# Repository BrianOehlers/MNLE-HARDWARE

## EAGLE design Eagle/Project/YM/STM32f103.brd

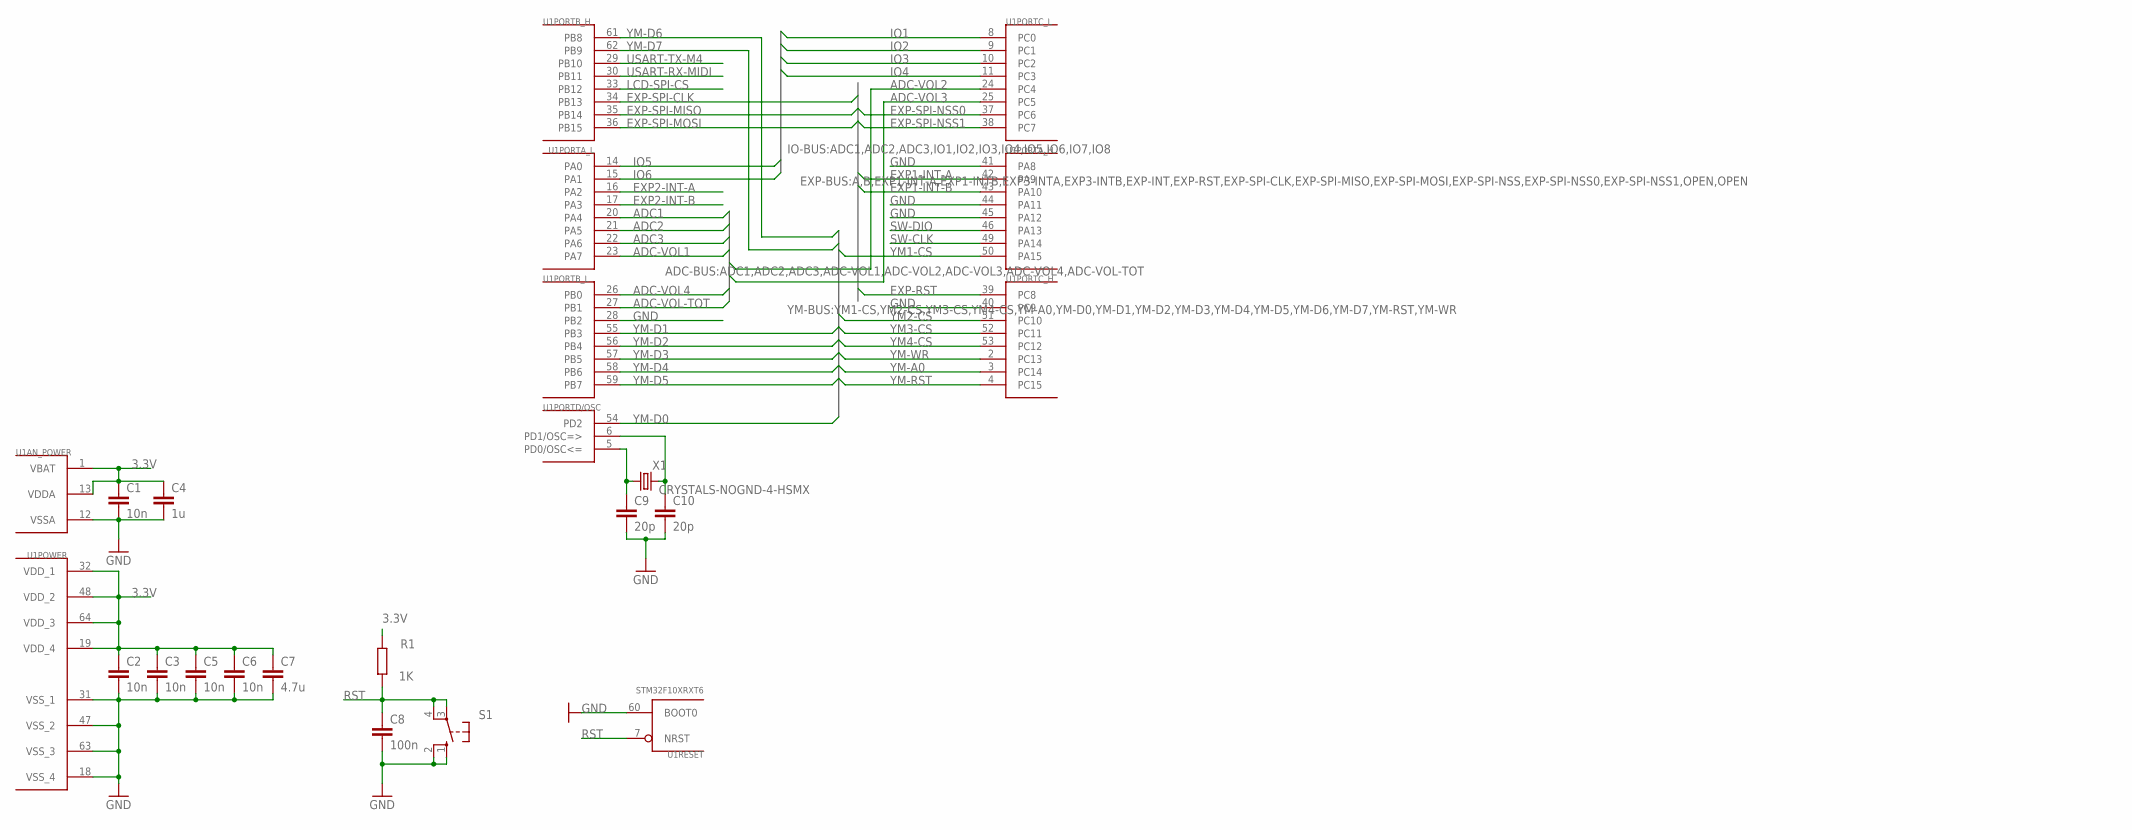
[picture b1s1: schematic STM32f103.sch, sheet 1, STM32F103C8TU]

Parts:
C1, C2, C3, C5, C6: 10n; C0603
C4: 1u; C0603
C7: 4.7u; C0603
C8: 100n; 0603-SMD
C9, C10: 20p; C0603
R1: 1K; 0805-SMD
S1: 10-XX; B3F-10XX
U1: STM32F10XRXT6; TQFP64
X1: CRYSTALS-NOGND-4-HSMX; HC49-4-HSMX

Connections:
3.3V: C1.1, C2.1, C3.1, C4.1, C5.1, C6.1, C7.1, R1.2, U1.1 (VBAT), U1.13 (VDDA), U1.19 (VDD_4), U1.32 (VDD_1), U1.48 (VDD_2), U1.64 (VDD_3); also elsewhere on the board
ADC1: U1.20 (PA4); also elsewhere on the board
ADC2: U1.21 (PA5); also elsewhere on the board
ADC3: U1.22 (PA6); also elsewhere on the board
ADC-VOL1: U1.23 (PA7); also elsewhere on the board
ADC-VOL2: U1.24 (PC4); also elsewhere on the board
ADC-VOL3: U1.25 (PC5); also elsewhere on the board
ADC-VOL4: U1.26 (PB0); also elsewhere on the board
ADC-VOL-TOT: U1.27 (PB1); also elsewhere on the board
EXP1-INT-A: U1.42 (PA9); also elsewhere on the board
EXP1-INT-B: U1.43 (PA10); also elsewhere on the board
EXP2-INT-A: U1.16 (PA2); also elsewhere on the board
EXP2-INT-B: U1.17 (PA3); also elsewhere on the board
EXP-RST: U1.39 (PC8); also elsewhere on the board
EXP-SPI-CLK: U1.34 (PB13); also elsewhere on the board
EXP-SPI-MISO: U1.35 (PB14); also elsewhere on the board
EXP-SPI-MOSI: U1.36 (PB15); also elsewhere on the board
EXP-SPI-NSS0: U1.37 (PC6); also elsewhere on the board
EXP-SPI-NSS1: U1.38 (PC7); also elsewhere on the board
GND: C1.2, C2.2, C3.2, C4.2, C5.2, C6.2, C7.2, C8.2, C9.2, C10.2, S1.1 (S), S1.2 (S1), U1.12 (VSSA), U1.18 (VSS_4), U1.28 (PB2), U1.31 (VSS_1), U1.40 (PC9), U1.41 (PA8), U1.44 (PA11), U1.45 (PA12), U1.47 (VSS_2), U1.60 (BOOT0), U1.63 (VSS_3); also elsewhere on the board
IO1: U1.8 (PC0); also elsewhere on the board
IO2: U1.9 (PC1); also elsewhere on the board
IO3: U1.10 (PC2); also elsewhere on the board
IO4: U1.11 (PC3); also elsewhere on the board
IO5: U1.14 (PA0); also elsewhere on the board
IO6: U1.15 (PA1); also elsewhere on the board
LCD-SPI-CS: U1.33 (PB12); also elsewhere on the board
unnamed: C9.1, U1.5 (PD0/OSC<=), X1.1
unnamed: C10.1, U1.6 (PD1/OSC=>), X1.2
RST: C8.1, R1.1, S1.3, S1.4 (P1), U1.7 (NRST)
SW-CLK: U1.49 (PA14); also elsewhere on the board
SW-DIO: U1.46 (PA13); also elsewhere on the board
USART-RX-MIDI: U1.30 (PB11); also elsewhere on the board
USART-TX-M4: U1.29 (PB10); also elsewhere on the board
YM1-CS: U1.50 (PA15); also elsewhere on the board
YM2-CS: U1.51 (PC10); also elsewhere on the board
YM3-CS: U1.52 (PC11); also elsewhere on the board
YM4-CS: U1.53 (PC12); also elsewhere on the board
YM-A0: U1.3 (PC14); also elsewhere on the board
YM-D0: U1.54 (PD2); also elsewhere on the board
YM-D1: U1.55 (PB3); also elsewhere on the board
YM-D2: U1.56 (PB4); also elsewhere on the board
YM-D3: U1.57 (PB5); also elsewhere on the board
YM-D4: U1.58 (PB6); also elsewhere on the board
YM-D5: U1.59 (PB7); also elsewhere on the board
YM-D6: U1.61 (PB8); also elsewhere on the board
YM-D7: U1.62 (PB9); also elsewhere on the board
YM-RST: U1.4 (PC15); also elsewhere on the board
YM-WR: U1.2 (PC13); also elsewhere on the board

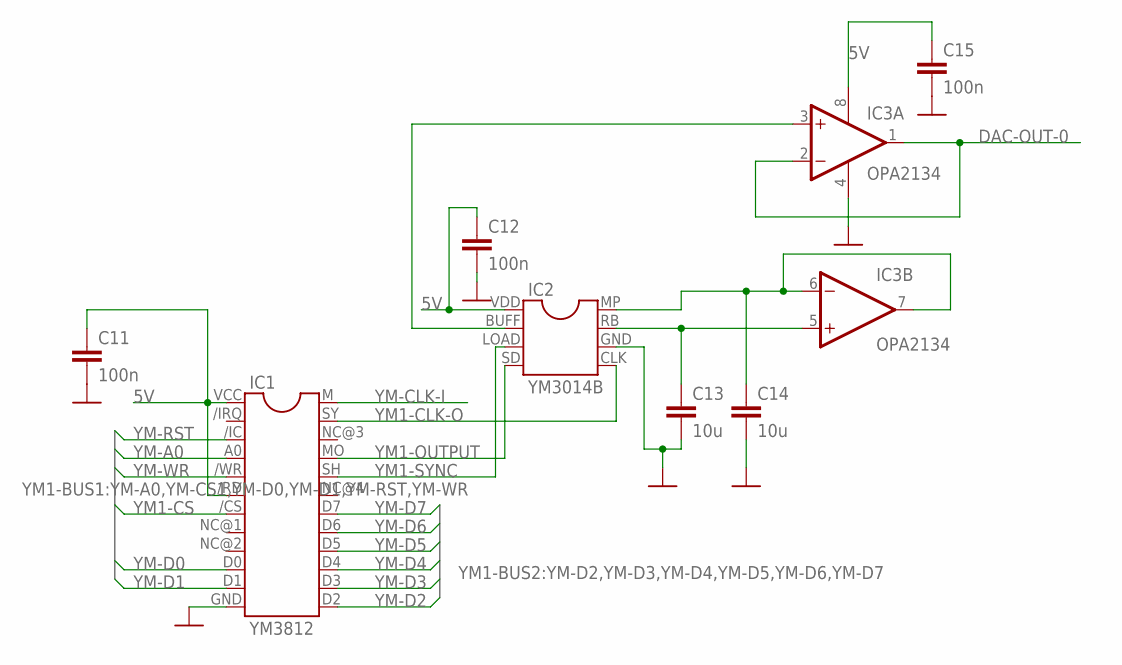
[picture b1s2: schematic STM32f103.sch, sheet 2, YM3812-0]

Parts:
C11, C12, C15: 100n; 0603-SMD
C13, C14: 10u; 0603-SMD
IC1: YM3812
IC2: YM3014B
IC3: OPA2134; DIL08

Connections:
5V: C11.1, C12.1, C15.1, IC1./RD, IC1.VCC, IC2.VDD, IC3.8 (V+); also elsewhere on the board
DAC-OUT-0: IC3.1 (OUT), IC3.2 (-IN); also elsewhere on the board
GND: C11.2, C12.2, C13.2, C14.2, C15.2, IC1.GND, IC2.GND, IC3.4 (V-); also elsewhere on the board
unnamed: IC2.BUFF, IC3.3 (+IN)
unnamed: C14.1, IC2.MP, IC3.6 (-IN), IC3.7 (OUT)
unnamed: C13.1, IC2.RB, IC3.5 (+IN)
YM1-CLK-O: IC1.SY, IC2.CLK
YM1-CS: IC1./CS; also elsewhere on the board
YM1-OUTPUT: IC1.MO, IC2.SD; also elsewhere on the board
YM1-SYNC: IC1.SH, IC2.LOAD; also elsewhere on the board
YM-A0: IC1.A0; also elsewhere on the board
YM-CLK-I: IC1.M; also elsewhere on the board
YM-D0: IC1.D0; also elsewhere on the board
YM-D1: IC1.D1; also elsewhere on the board
YM-D2: IC1.D2; also elsewhere on the board
YM-D3: IC1.D3; also elsewhere on the board
YM-D4: IC1.D4; also elsewhere on the board
YM-D5: IC1.D5; also elsewhere on the board
YM-D6: IC1.D6; also elsewhere on the board
YM-D7: IC1.D7; also elsewhere on the board
YM-RST: IC1./IC; also elsewhere on the board
YM-WR: IC1./WR; also elsewhere on the board

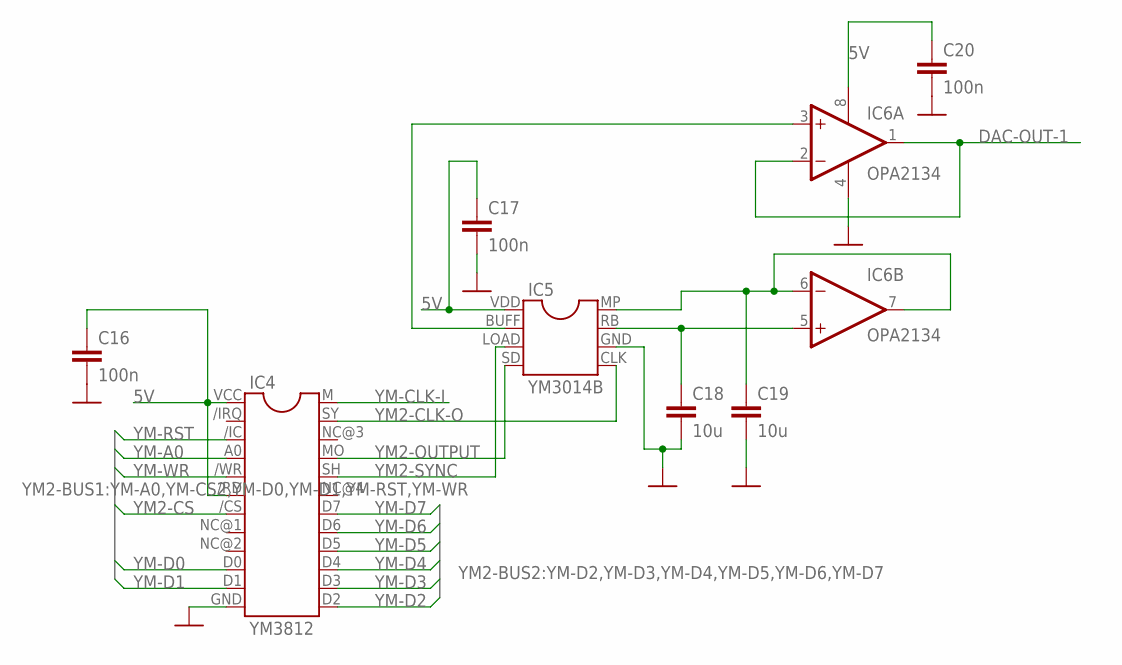
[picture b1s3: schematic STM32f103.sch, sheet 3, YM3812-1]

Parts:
C16, C17, C20: 100n; 0603-SMD
C18, C19: 10u; 0603-SMD
IC4: YM3812
IC5: YM3014B
IC6: OPA2134; DIL08

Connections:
5V: C16.1, C17.1, C20.1, IC4./RD, IC4.VCC, IC5.VDD, IC6.8 (V+); also elsewhere on the board
DAC-OUT-1: IC6.1 (OUT), IC6.2 (-IN); also elsewhere on the board
GND: C16.2, C17.2, C18.2, C19.2, C20.2, IC4.GND, IC5.GND, IC6.4 (V-); also elsewhere on the board
unnamed: C18.1, IC5.RB, IC6.5 (+IN)
unnamed: IC5.BUFF, IC6.3 (+IN)
unnamed: C19.1, IC5.MP, IC6.6 (-IN), IC6.7 (OUT)
YM2-CLK-O: IC4.SY, IC5.CLK
YM2-CS: IC4./CS; also elsewhere on the board
YM2-OUTPUT: IC4.MO, IC5.SD; also elsewhere on the board
YM2-SYNC: IC4.SH, IC5.LOAD; also elsewhere on the board
YM-A0: IC4.A0; also elsewhere on the board
YM-CLK-I: IC4.M; also elsewhere on the board
YM-D0: IC4.D0; also elsewhere on the board
YM-D1: IC4.D1; also elsewhere on the board
YM-D2: IC4.D2; also elsewhere on the board
YM-D3: IC4.D3; also elsewhere on the board
YM-D4: IC4.D4; also elsewhere on the board
YM-D5: IC4.D5; also elsewhere on the board
YM-D6: IC4.D6; also elsewhere on the board
YM-D7: IC4.D7; also elsewhere on the board
YM-RST: IC4./IC; also elsewhere on the board
YM-WR: IC4./WR; also elsewhere on the board

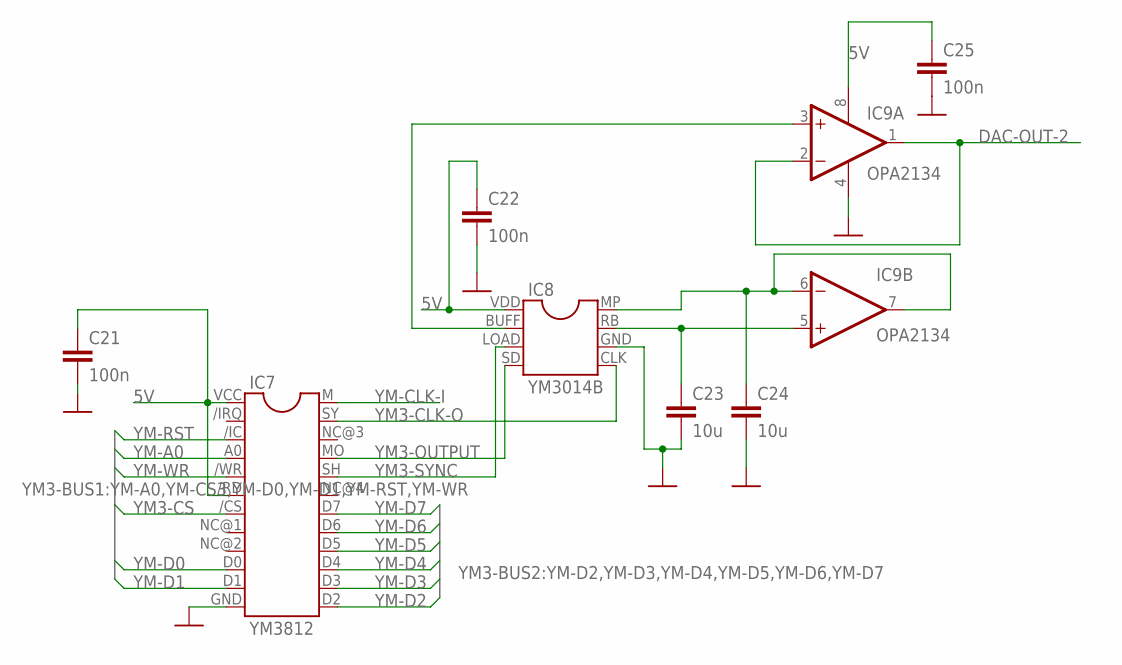
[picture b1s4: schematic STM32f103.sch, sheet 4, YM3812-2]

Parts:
C21, C22, C25: 100n; 0603-SMD
C23, C24: 10u; 0603-SMD
IC7: YM3812
IC8: YM3014B
IC9: OPA2134; DIL08

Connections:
5V: C21.1, C22.1, C25.1, IC7./RD, IC7.VCC, IC8.VDD, IC9.8 (V+); also elsewhere on the board
DAC-OUT-2: IC9.1 (OUT), IC9.2 (-IN); also elsewhere on the board
GND: C21.2, C22.2, C23.2, C24.2, C25.2, IC7.GND, IC8.GND, IC9.4 (V-); also elsewhere on the board
unnamed: C23.1, IC8.RB, IC9.5 (+IN)
unnamed: IC8.BUFF, IC9.3 (+IN)
unnamed: C24.1, IC8.MP, IC9.6 (-IN), IC9.7 (OUT)
YM3-CLK-O: IC7.SY, IC8.CLK
YM3-CS: IC7./CS; also elsewhere on the board
YM3-OUTPUT: IC7.MO, IC8.SD; also elsewhere on the board
YM3-SYNC: IC7.SH, IC8.LOAD; also elsewhere on the board
YM-A0: IC7.A0; also elsewhere on the board
YM-CLK-I: IC7.M; also elsewhere on the board
YM-D0: IC7.D0; also elsewhere on the board
YM-D1: IC7.D1; also elsewhere on the board
YM-D2: IC7.D2; also elsewhere on the board
YM-D3: IC7.D3; also elsewhere on the board
YM-D4: IC7.D4; also elsewhere on the board
YM-D5: IC7.D5; also elsewhere on the board
YM-D6: IC7.D6; also elsewhere on the board
YM-D7: IC7.D7; also elsewhere on the board
YM-RST: IC7./IC; also elsewhere on the board
YM-WR: IC7./WR; also elsewhere on the board

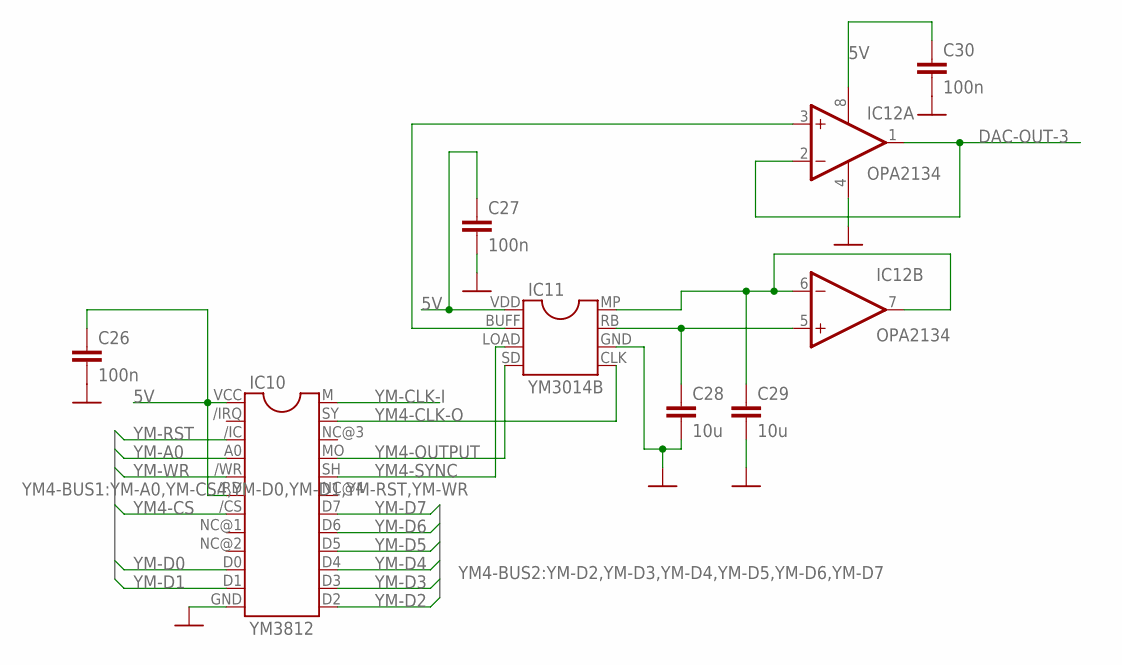
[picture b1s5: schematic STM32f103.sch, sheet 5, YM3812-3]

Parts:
C26, C27, C30: 100n; 0603-SMD
C28, C29: 10u; 0603-SMD
IC10: YM3812
IC11: YM3014B
IC12: OPA2134; DIL08

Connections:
5V: C26.1, C27.1, C30.1, IC10./RD, IC10.VCC, IC11.VDD, IC12.8 (V+); also elsewhere on the board
DAC-OUT-3: IC12.1 (OUT), IC12.2 (-IN); also elsewhere on the board
GND: C26.2, C27.2, C28.2, C29.2, C30.2, IC10.GND, IC11.GND, IC12.4 (V-); also elsewhere on the board
unnamed: C28.1, IC11.RB, IC12.5 (+IN)
unnamed: IC11.BUFF, IC12.3 (+IN)
unnamed: C29.1, IC11.MP, IC12.6 (-IN), IC12.7 (OUT)
YM4-CLK-O: IC10.SY, IC11.CLK
YM4-CS: IC10./CS; also elsewhere on the board
YM4-OUTPUT: IC10.MO, IC11.SD; also elsewhere on the board
YM4-SYNC: IC10.SH, IC11.LOAD; also elsewhere on the board
YM-A0: IC10.A0; also elsewhere on the board
YM-CLK-I: IC10.M; also elsewhere on the board
YM-D0: IC10.D0; also elsewhere on the board
YM-D1: IC10.D1; also elsewhere on the board
YM-D2: IC10.D2; also elsewhere on the board
YM-D3: IC10.D3; also elsewhere on the board
YM-D4: IC10.D4; also elsewhere on the board
YM-D5: IC10.D5; also elsewhere on the board
YM-D6: IC10.D6; also elsewhere on the board
YM-D7: IC10.D7; also elsewhere on the board
YM-RST: IC10./IC; also elsewhere on the board
YM-WR: IC10./WR; also elsewhere on the board

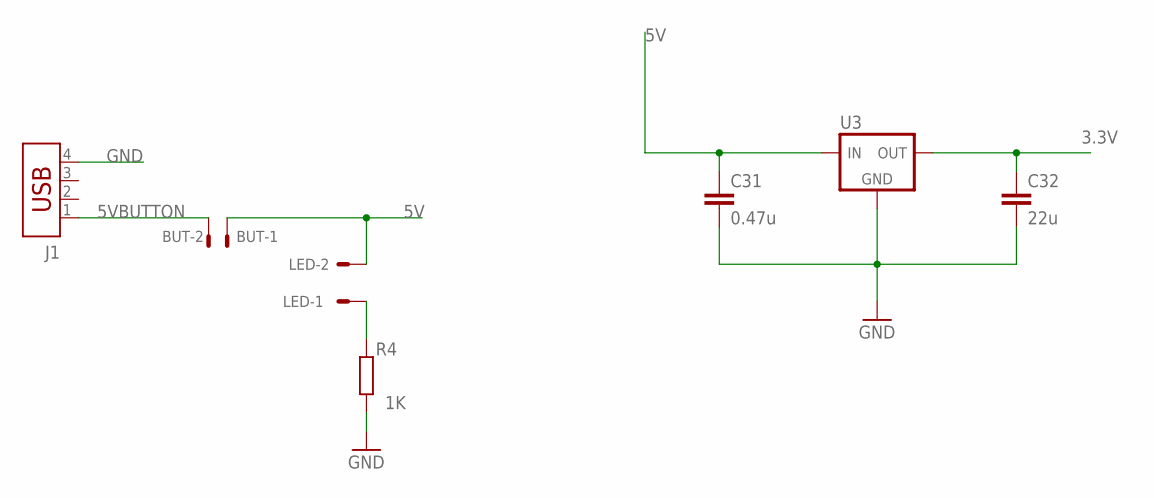
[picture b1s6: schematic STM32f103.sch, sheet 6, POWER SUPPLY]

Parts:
BUT: 22-27-2021-02; 6410-02
C31: 0.47u; 0603-SMD
C32: 22u; 0603-SMD
J1: CON-USB-B; USB-B
LED: 22-27-2021-02; 6410-02
R4: 1K; 0805-SMD
U3: LM2931AT-H; TO220BH

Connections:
3.3V: C32.1, U3.3 (VOUT); also elsewhere on the board
5V: BUT.1, C31.1, LED.2, U3.1 (VIN); also elsewhere on the board
5VBUTTON: BUT.2, J1.1
GND: C31.2, C32.2, J1.4, R4.2, U3.2 (GND); also elsewhere on the board
unnamed: LED.1, R4.1

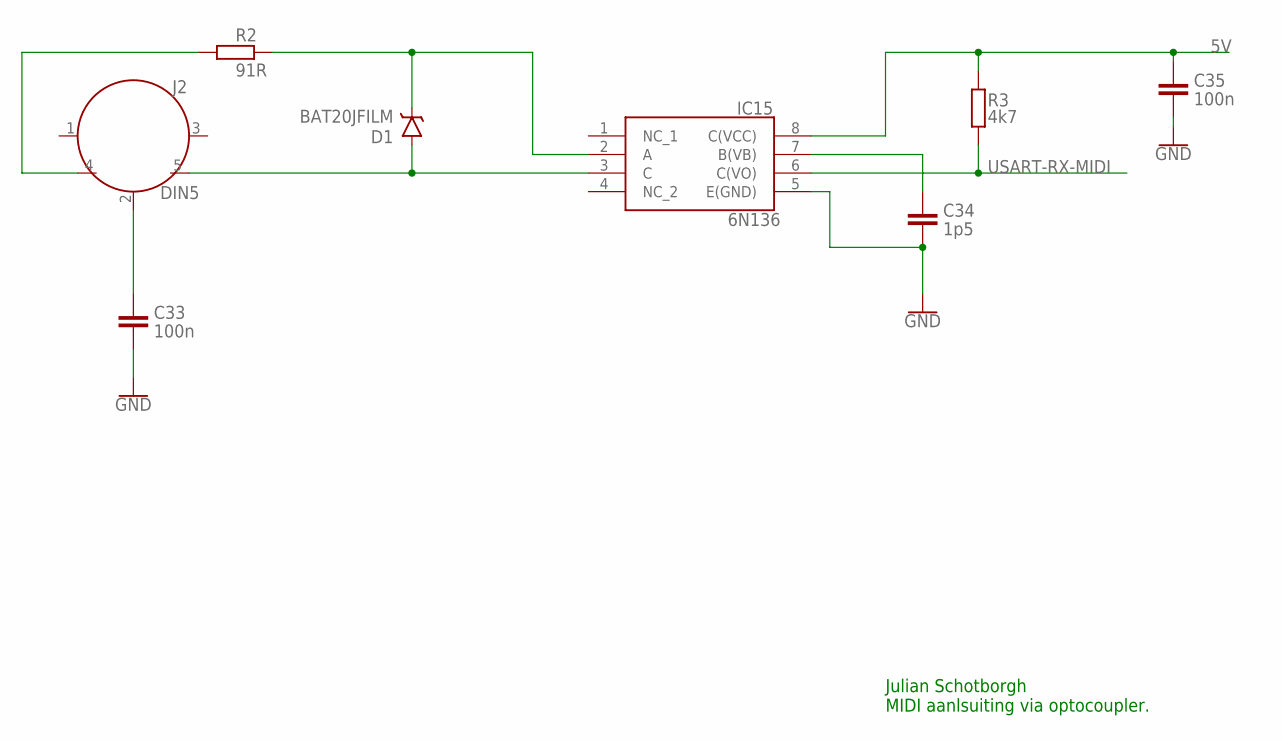
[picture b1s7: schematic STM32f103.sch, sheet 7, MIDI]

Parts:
C33, C35: 100n; C0603
C34: 1p5; C0603
D1: BAT20JFILM; SOD-323
IC15: 6N136; DIP762W60P254L1060H465Q8N
J2: DIN5; DIN5-RA-PTH
R2: 91R; 0805-SMD
R3: 4k7; 0805-SMD

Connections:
5V: C35.2, IC15.8 (C(VCC)), R3.1; also elsewhere on the board
GND: C33.2, C34.1, C35.1, IC15.5 (E(GND)); also elsewhere on the board
unnamed: D1.A, IC15.3 (C), J2.5
unnamed: D1.C, IC15.2 (A), R2.2
unnamed: C33.1, J2.2
unnamed: J2.4, R2.1
unnamed: C34.2, IC15.7 (B(VB))
USART-RX-MIDI: IC15.6 (C(VO)), R3.2; also elsewhere on the board

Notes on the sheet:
Julian Schotborgh MIDI aanlsuiting via optocoupler.

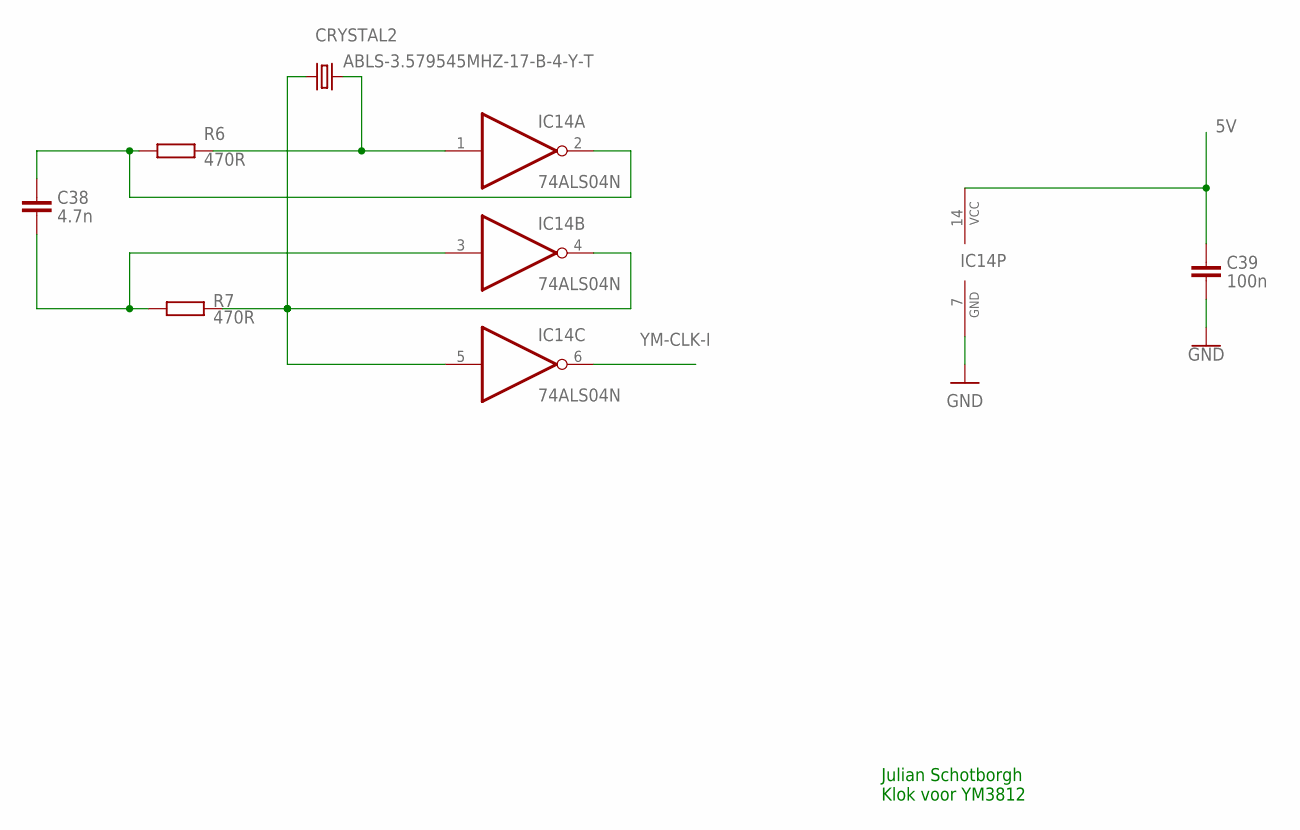
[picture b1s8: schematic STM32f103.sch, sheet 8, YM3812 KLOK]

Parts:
C38: 4.7n; C0603
C39: 100n; C0603
CRYSTAL2: ABLS-3.579545MHZ-17-B-4-Y-T; ABLS-3.579545MHZ-17-B-4-Y-T-11.5X4.7X4.2
IC14: 74ALS04N; DIL14
R6, R7: 470R; 0805-SMD

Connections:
5V: C39.2, IC14.14 (VCC); also elsewhere on the board
GND: C39.1, IC14.7 (GND); also elsewhere on the board
unnamed: CRYSTAL2.P$1 (1), IC14.4 (O), IC14.5 (I), R7.2
unnamed: C38.2, IC14.2 (O), R6.1
unnamed: C38.1, IC14.3 (I), R7.1
unnamed: CRYSTAL2.P$2 (2), IC14.1 (I), R6.2
YM-CLK-I: IC14.6 (O); also elsewhere on the board

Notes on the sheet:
Julian Schotborgh Klok voor YM3812

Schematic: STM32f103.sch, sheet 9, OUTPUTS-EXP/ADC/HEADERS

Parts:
SL1, SL2, SL3, SL4, SL5, SL6, SL7, SL8: MA03; 03P
SL9: M06; 06P
SV2: MA04-1
SV3: 2514-6002UB; 3M_2514-6002UB
SV4: FE13-1; FE13
SV6: FE06-1; FE06
SV7: FE12-1; FE12

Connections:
3.3V: SL1.1, SL2.1, SL3.1, SL4.1, SL5.1, SL6.1, SL7.1, SL8.1, SV2.1, SV3.4, SV4.2, SV4.12; also elsewhere on the board
5V: SL9.5, SV3.3, SV4.3, SV4.13, SV7.11; also elsewhere on the board
ADC1: SL6.2; also elsewhere on the board
ADC2: SL7.2; also elsewhere on the board
ADC3: SL8.2; also elsewhere on the board
ADC-VOL1: SL2.2; also elsewhere on the board
ADC-VOL2: SL3.2; also elsewhere on the board
ADC-VOL3: SL4.2; also elsewhere on the board
ADC-VOL4: SL5.2; also elsewhere on the board
ADC-VOL-TOT: SL1.2; also elsewhere on the board
DAC-OUT-0: SV6.1; also elsewhere on the board
DAC-OUT-1: SV6.2; also elsewhere on the board
DAC-OUT-2: SV6.3; also elsewhere on the board
DAC-OUT-3: SV6.4; also elsewhere on the board
EXP1-INT-A: SV3.8; also elsewhere on the board
EXP1-INT-B: SV3.7; also elsewhere on the board
EXP2-INT-A: SV3.5; also elsewhere on the board
EXP2-INT-B: SV3.6; also elsewhere on the board
EXP-RST: SV3.9; also elsewhere on the board
EXP-SPI-CLK: SL9.2, SV3.14; also elsewhere on the board
EXP-SPI-MISO: SL9.3, SV3.13; also elsewhere on the board
EXP-SPI-MOSI: SL9.4, SV3.12; also elsewhere on the board
EXP-SPI-NSS0: SV3.11; also elsewhere on the board
EXP-SPI-NSS1: SV3.10; also elsewhere on the board
GND: SL1.3, SL2.3, SL3.3, SL4.3, SL5.3, SL6.3, SL7.3, SL8.3, SL9.6, SV2.4, SV3.2, SV4.1, SV4.11, SV6.6, SV7.12; also elsewhere on the board
IO1: SV4.10; also elsewhere on the board
IO2: SV4.9; also elsewhere on the board
IO3: SV4.8; also elsewhere on the board
IO4: SV4.7; also elsewhere on the board
IO5: SV4.6; also elsewhere on the board
IO6: SV4.5; also elsewhere on the board
LCD-SPI-CS: SL9.1; also elsewhere on the board
OPEN: SV3.1
SW-CLK: SV2.3; also elsewhere on the board
SW-DIO: SV2.2; also elsewhere on the board
USART-TX-M4: SV4.4, SV7.10; also elsewhere on the board
YM1-OUTPUT: SV7.2; also elsewhere on the board
YM1-SYNC: SV7.6; also elsewhere on the board
YM2-OUTPUT: SV7.3; also elsewhere on the board
YM2-SYNC: SV7.7; also elsewhere on the board
YM3-OUTPUT: SV7.4; also elsewhere on the board
YM3-SYNC: SV7.8; also elsewhere on the board
YM4-OUTPUT: SV7.5; also elsewhere on the board
YM4-SYNC: SV7.9; also elsewhere on the board
YM-CLK-I: SV7.1; also elsewhere on the board

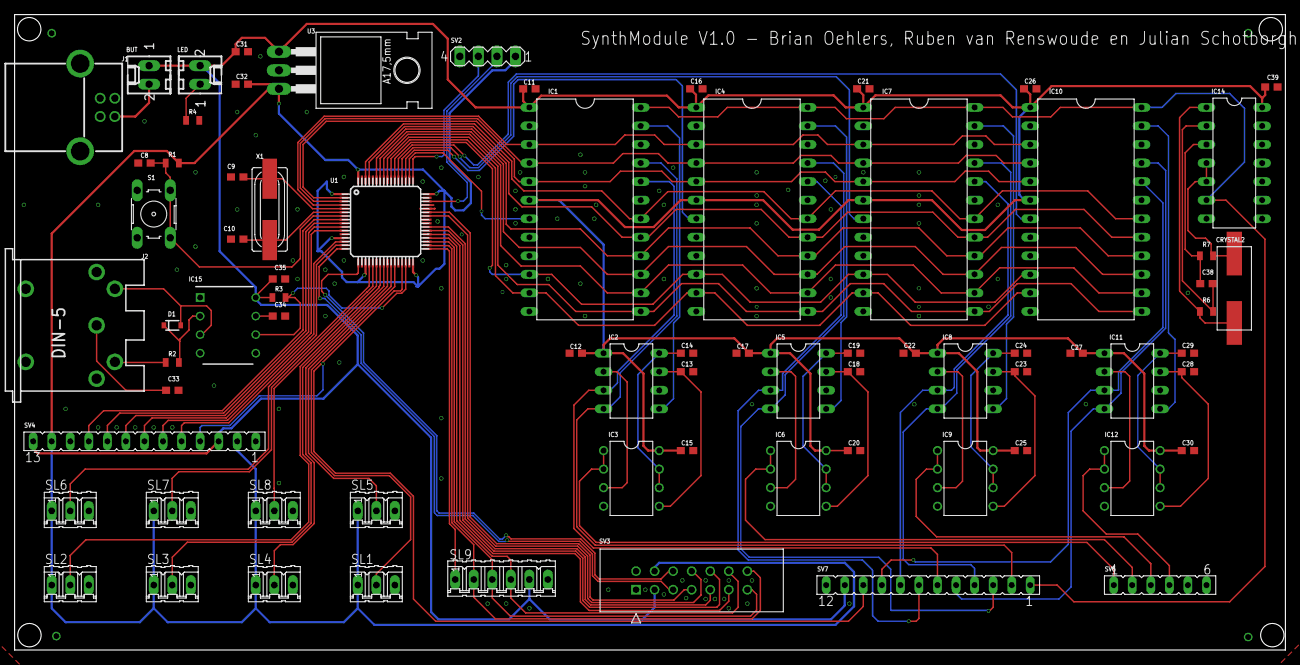
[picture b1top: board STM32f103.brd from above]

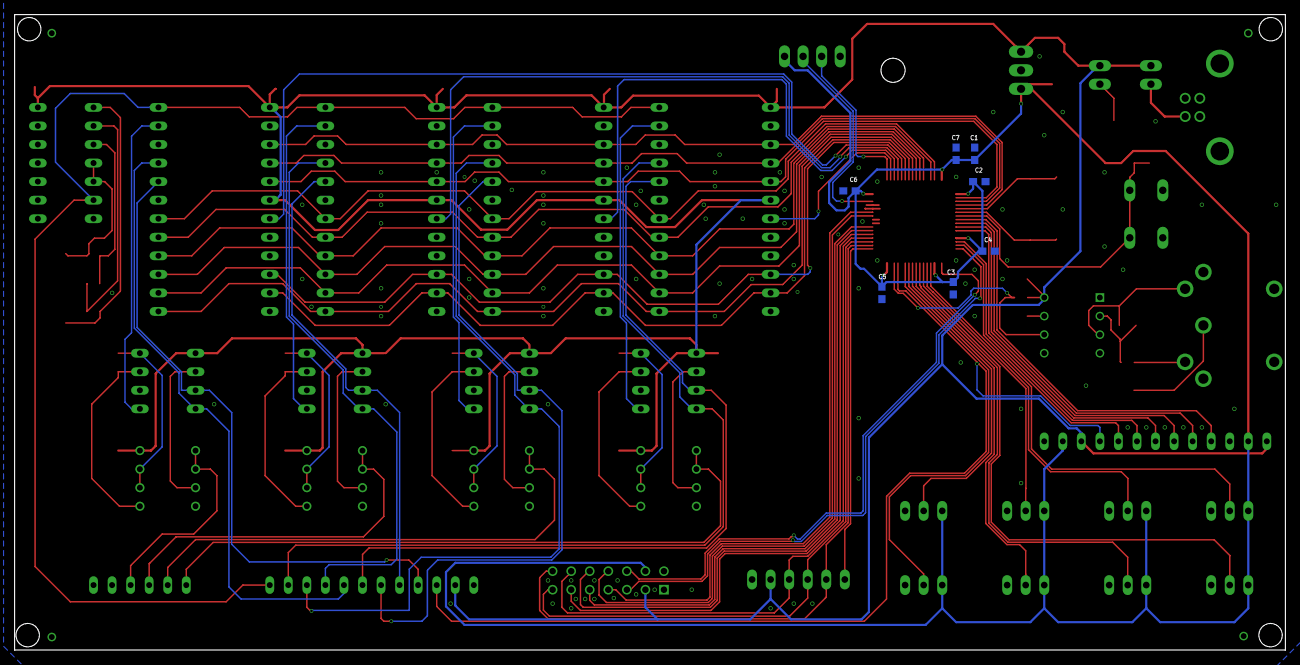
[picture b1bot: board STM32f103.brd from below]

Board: 2 copper layers, 174.0 x 87.0 mm, 81 parts (7 on the bottom side), 90 nets.

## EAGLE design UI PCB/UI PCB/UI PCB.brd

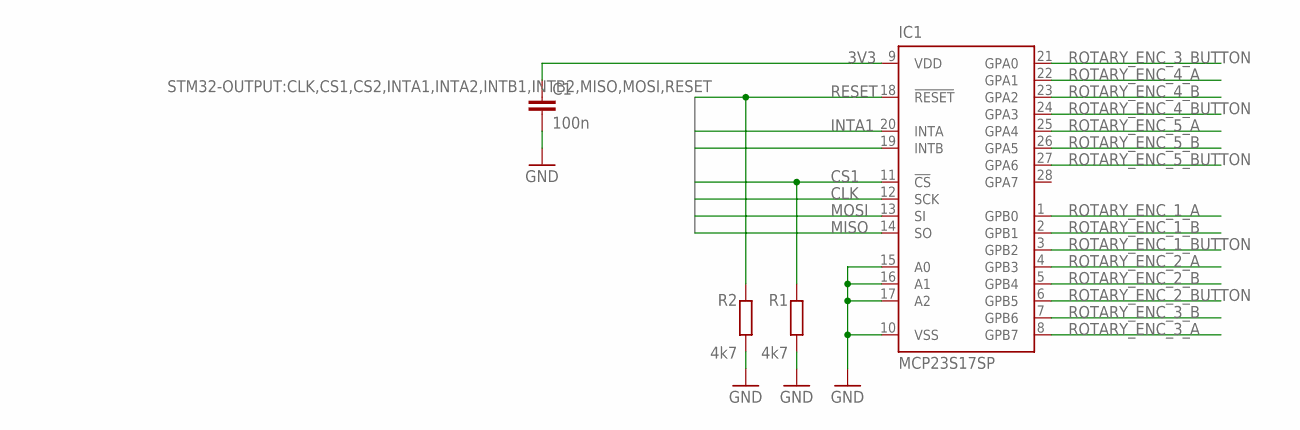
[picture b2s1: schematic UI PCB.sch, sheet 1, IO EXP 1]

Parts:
C1: 100n; C0603
IC1: MCP23S17SP; DIL28-3
R1, R2: 4k7; R0805

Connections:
3V3: C1.1, IC1.9 (VDD); also elsewhere on the board
CLK: IC1.12 (SCK); also elsewhere on the board
CS1: IC1.11 (!CS), R1.2; also elsewhere on the board
GND: C1.2, IC1.10 (VSS), IC1.15 (A0), IC1.16 (A1), IC1.17 (A2), R1.1, R2.1; also elsewhere on the board
INTA1: IC1.20 (INTA); also elsewhere on the board
INTB1: IC1.19 (INTB); also elsewhere on the board
MISO: IC1.14 (SO); also elsewhere on the board
MOSI: IC1.13 (SI); also elsewhere on the board
RESET: IC1.18 (!RESET), R2.2; also elsewhere on the board
ROTARY_ENC_1_A: IC1.1 (GPB0); also elsewhere on the board
ROTARY_ENC_1_B: IC1.2 (GPB1); also elsewhere on the board
ROTARY_ENC_1_BUTTON: IC1.3 (GPB2); also elsewhere on the board
ROTARY_ENC_2_A: IC1.4 (GPB3); also elsewhere on the board
ROTARY_ENC_2_B: IC1.5 (GPB4); also elsewhere on the board
ROTARY_ENC_2_BUTTON: IC1.6 (GPB5); also elsewhere on the board
ROTARY_ENC_3_A: IC1.8 (GPB7); also elsewhere on the board
ROTARY_ENC_3_B: IC1.7 (GPB6); also elsewhere on the board
ROTARY_ENC_3_BUTTON: IC1.21 (GPA0); also elsewhere on the board
ROTARY_ENC_4_A: IC1.22 (GPA1); also elsewhere on the board
ROTARY_ENC_4_B: IC1.23 (GPA2); also elsewhere on the board
ROTARY_ENC_4_BUTTON: IC1.24 (GPA3); also elsewhere on the board
ROTARY_ENC_5_A: IC1.25 (GPA4); also elsewhere on the board
ROTARY_ENC_5_B: IC1.26 (GPA5); also elsewhere on the board
ROTARY_ENC_5_BUTTON: IC1.27 (GPA6); also elsewhere on the board

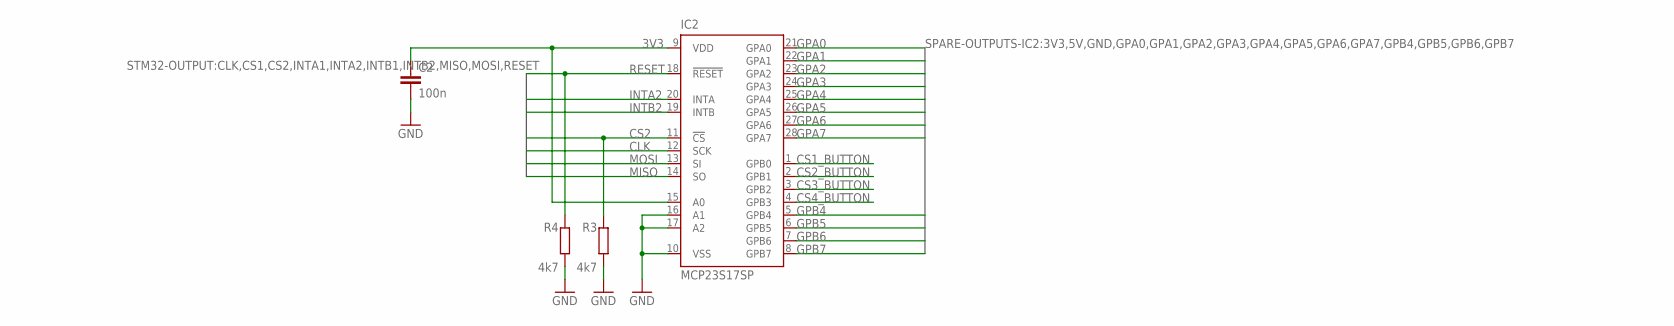
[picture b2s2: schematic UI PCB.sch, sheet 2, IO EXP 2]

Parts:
C2: 100n; C0603
IC2: MCP23S17SP; DIL28-3
R3, R4: 4k7; R0805

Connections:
3V3: C2.1, IC2.9 (VDD), IC2.15 (A0); also elsewhere on the board
CLK: IC2.12 (SCK); also elsewhere on the board
CS1_BUTTON: IC2.1 (GPB0); also elsewhere on the board
CS2: IC2.11 (!CS), R3.2; also elsewhere on the board
CS2_BUTTON: IC2.2 (GPB1); also elsewhere on the board
CS3_BUTTON: IC2.3 (GPB2); also elsewhere on the board
CS4_BUTTON: IC2.4 (GPB3); also elsewhere on the board
GND: C2.2, IC2.10 (VSS), IC2.16 (A1), IC2.17 (A2), R3.1, R4.1; also elsewhere on the board
GPA0: IC2.21 (GPA0); also elsewhere on the board
GPA1: IC2.22 (GPA1); also elsewhere on the board
GPA2: IC2.23 (GPA2); also elsewhere on the board
GPA3: IC2.24 (GPA3); also elsewhere on the board
GPA4: IC2.25 (GPA4); also elsewhere on the board
GPA5: IC2.26 (GPA5); also elsewhere on the board
GPA6: IC2.27 (GPA6); also elsewhere on the board
GPA7: IC2.28 (GPA7); also elsewhere on the board
GPB4: IC2.5 (GPB4); also elsewhere on the board
GPB5: IC2.6 (GPB5); also elsewhere on the board
GPB6: IC2.7 (GPB6); also elsewhere on the board
GPB7: IC2.8 (GPB7); also elsewhere on the board
INTA2: IC2.20 (INTA); also elsewhere on the board
INTB2: IC2.19 (INTB); also elsewhere on the board
MISO: IC2.14 (SO); also elsewhere on the board
MOSI: IC2.13 (SI); also elsewhere on the board
RESET: IC2.18 (!RESET), R4.2; also elsewhere on the board

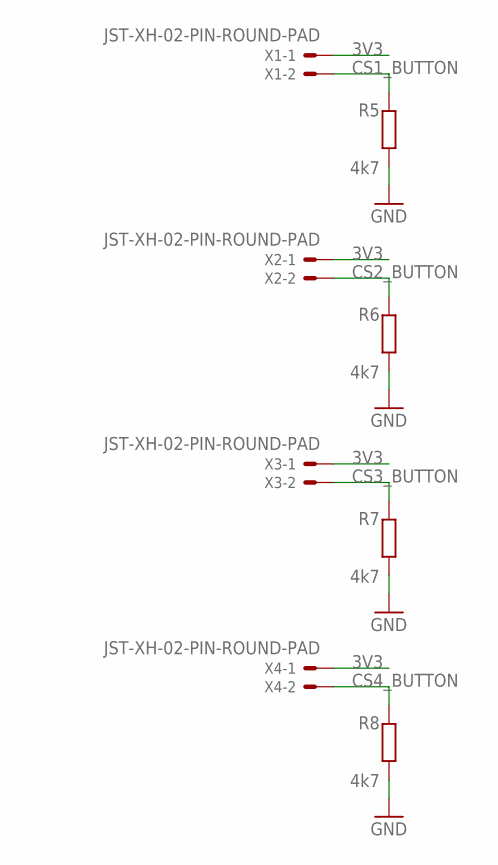
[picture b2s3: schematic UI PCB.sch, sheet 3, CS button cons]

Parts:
R5, R6, R7, R8: 4k7; R0805
X1, X2, X3, X4: JST-XH-02-PIN-ROUND-PAD; JST-XH-02-PACKAGE-ROUND-PAD

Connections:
3V3: X1.1, X2.1, X3.1, X4.1; also elsewhere on the board
CS1_BUTTON: R5.2, X1.2; also elsewhere on the board
CS2_BUTTON: R6.2, X2.2; also elsewhere on the board
CS3_BUTTON: R7.2, X3.2; also elsewhere on the board
CS4_BUTTON: R8.2, X4.2; also elsewhere on the board
GND: R5.1, R6.1, R7.1, R8.1; also elsewhere on the board

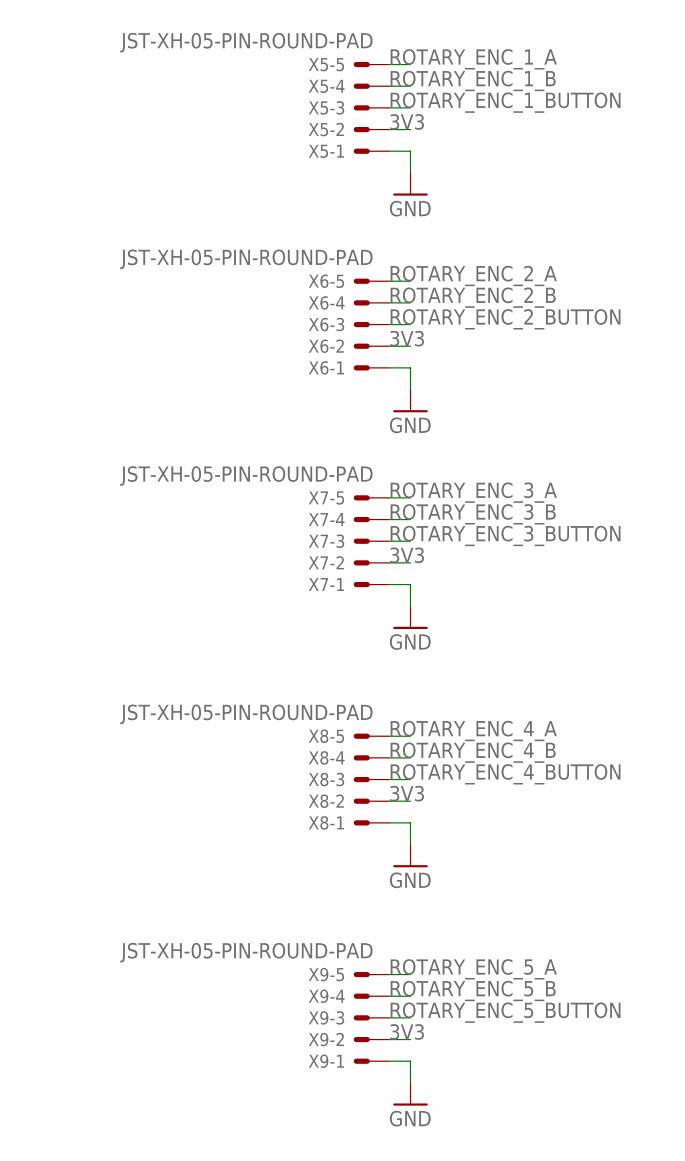
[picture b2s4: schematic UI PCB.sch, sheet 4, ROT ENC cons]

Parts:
X5, X6, X7, X8, X9: JST-XH-05-PIN-ROUND-PAD; JST-XH-05-PACKAGE-ROUND-PAD

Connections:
3V3: X5.2, X6.2, X7.2, X8.2, X9.2; also elsewhere on the board
GND: X5.1, X6.1, X7.1, X8.1, X9.1; also elsewhere on the board
ROTARY_ENC_1_A: X5.5; also elsewhere on the board
ROTARY_ENC_1_B: X5.4; also elsewhere on the board
ROTARY_ENC_1_BUTTON: X5.3; also elsewhere on the board
ROTARY_ENC_2_A: X6.5; also elsewhere on the board
ROTARY_ENC_2_B: X6.4; also elsewhere on the board
ROTARY_ENC_2_BUTTON: X6.3; also elsewhere on the board
ROTARY_ENC_3_A: X7.5; also elsewhere on the board
ROTARY_ENC_3_B: X7.4; also elsewhere on the board
ROTARY_ENC_3_BUTTON: X7.3; also elsewhere on the board
ROTARY_ENC_4_A: X8.5; also elsewhere on the board
ROTARY_ENC_4_B: X8.4; also elsewhere on the board
ROTARY_ENC_4_BUTTON: X8.3; also elsewhere on the board
ROTARY_ENC_5_A: X9.5; also elsewhere on the board
ROTARY_ENC_5_B: X9.4; also elsewhere on the board
ROTARY_ENC_5_BUTTON: X9.3; also elsewhere on the board

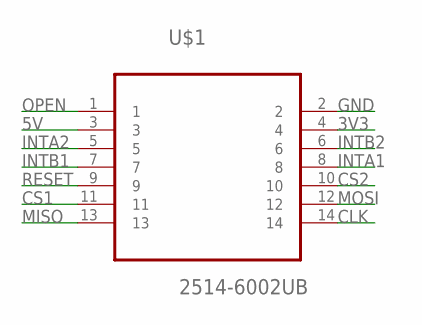
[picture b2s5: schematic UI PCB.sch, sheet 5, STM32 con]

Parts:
U$1: 2514-6002UB; 3M_2514-6002UB

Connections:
3V3: U$1.4; also elsewhere on the board
5V: U$1.3; also elsewhere on the board
CLK: U$1.14; also elsewhere on the board
CS1: U$1.11; also elsewhere on the board
CS2: U$1.10; also elsewhere on the board
GND: U$1.2; also elsewhere on the board
INTA1: U$1.8; also elsewhere on the board
INTA2: U$1.5; also elsewhere on the board
INTB1: U$1.7; also elsewhere on the board
INTB2: U$1.6; also elsewhere on the board
MISO: U$1.13; also elsewhere on the board
MOSI: U$1.12; also elsewhere on the board
OPEN: U$1.1
RESET: U$1.9; also elsewhere on the board

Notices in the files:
parts and their libraries:
LDO: License : GNU General Public License version 2 (see bottom)
SparkFun-Connectors: Licensing: Creative Commons ShareAlike 4.0 International - https://creativecommons.org/licenses/by-sa/4.0
